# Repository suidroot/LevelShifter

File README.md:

# LevelShifter
A Board Design for the SN74LVC244 chip to shift from 5v to 3.3v

This design was built out in Kicad

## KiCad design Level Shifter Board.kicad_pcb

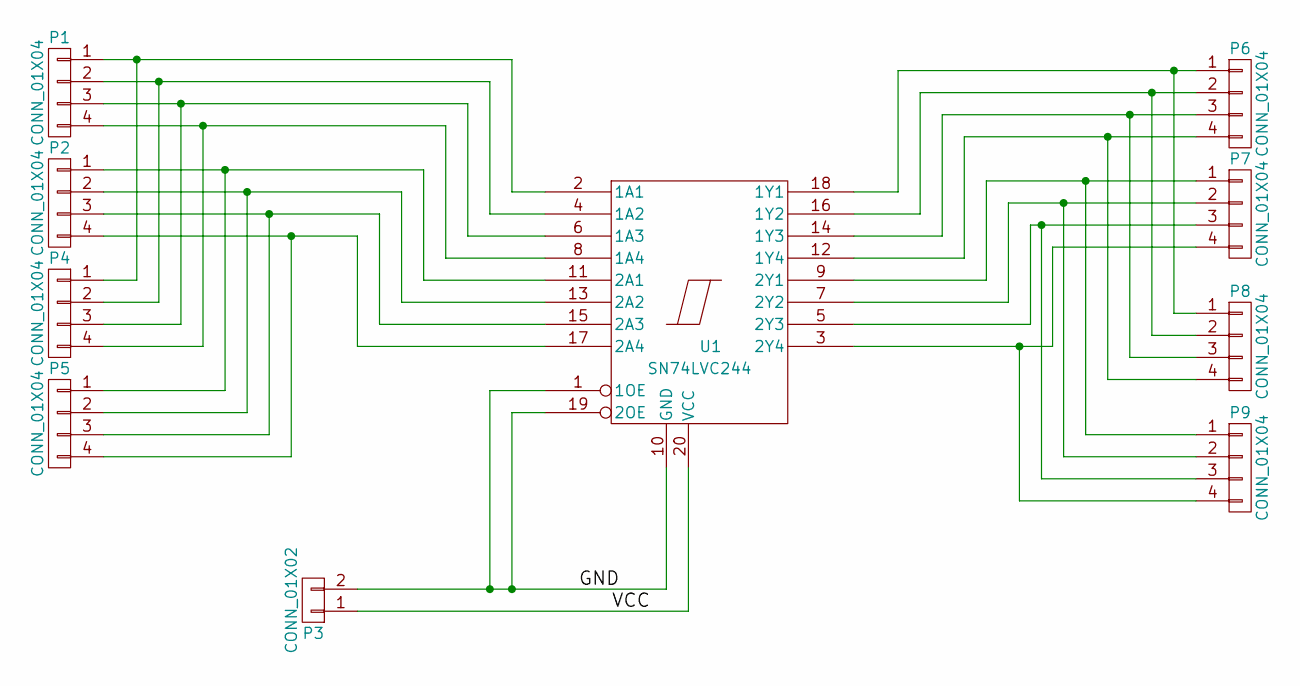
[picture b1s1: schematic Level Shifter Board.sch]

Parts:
P1, P2, P4, P5, P6, P7, P8, P9: CONN_01X04; Socket_Strip_Straight_1x04_Pitch2.54mm
P3: CONN_01X02; Socket_Strip_Straight_1x02_Pitch2.54mm
U1: SN74LVC244; DIP-20_W7.62mm

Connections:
/GND: P3.2, U1.1 (1OE), U1.10 (GND), U1.19 (2OE)
/VCC: P3.1, U1.20 (VCC)
unnamed: P1.1, P4.1, U1.2 (1A1)
unnamed: P1.2, P4.2, U1.4 (1A2)
unnamed: P1.3, P4.3, U1.6 (1A3)
unnamed: P1.4, P4.4, U1.8 (1A4)
unnamed: P2.1, P5.1, U1.11 (2A1)
unnamed: P2.2, P5.2, U1.13 (2A2)
unnamed: P2.3, P5.3, U1.15 (2A3)
unnamed: P2.4, P5.4, U1.17 (2A4)
unnamed: P6.1, P8.1, U1.18 (1Y1)
unnamed: P6.2, P8.2, U1.16 (1Y2)
unnamed: P6.3, P8.3, U1.14 (1Y3)
unnamed: P6.4, P8.4, U1.12 (1Y4)
unnamed: P7.1, P9.1, U1.9 (2Y1)
unnamed: P7.2, P9.2, U1.7 (2Y2)
unnamed: P7.3, P9.3, U1.5 (2Y3)
unnamed: P7.4, P9.4, U1.3 (2Y4)

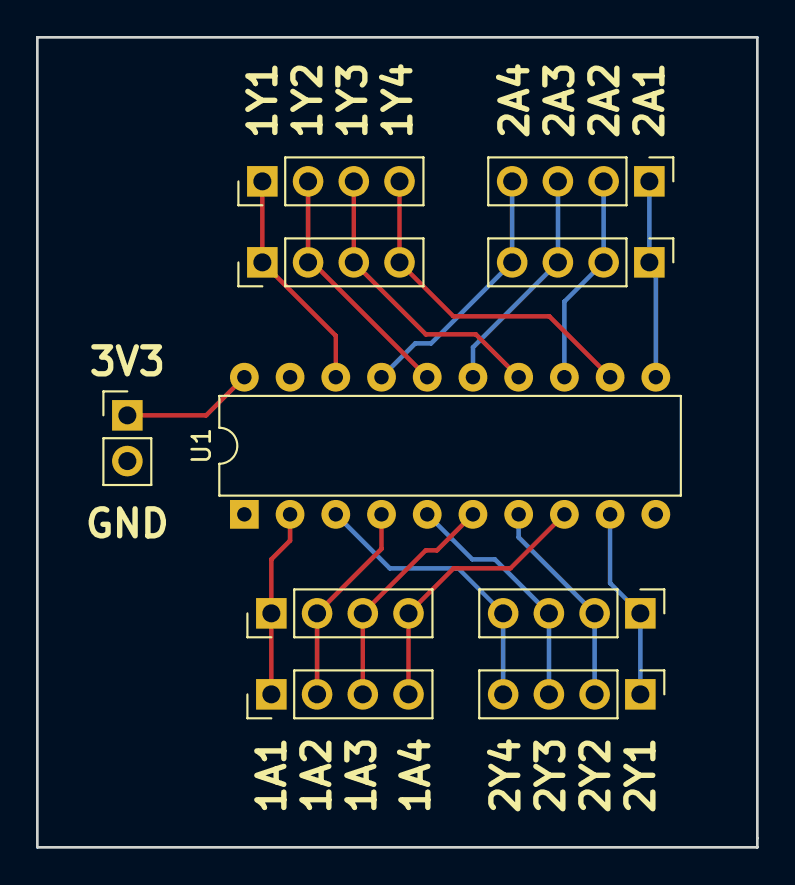
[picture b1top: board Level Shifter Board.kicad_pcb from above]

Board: 2 copper layers, 40.0 x 45.0 mm, 10 parts (0 on the bottom side), 18 nets.

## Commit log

2017-07-08 Removing GERBERS
